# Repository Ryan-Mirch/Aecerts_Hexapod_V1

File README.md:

# Aecerts-Hexapod-V1
# THIS IS A MESSY WIP, USE AT YOUR OWN RISK

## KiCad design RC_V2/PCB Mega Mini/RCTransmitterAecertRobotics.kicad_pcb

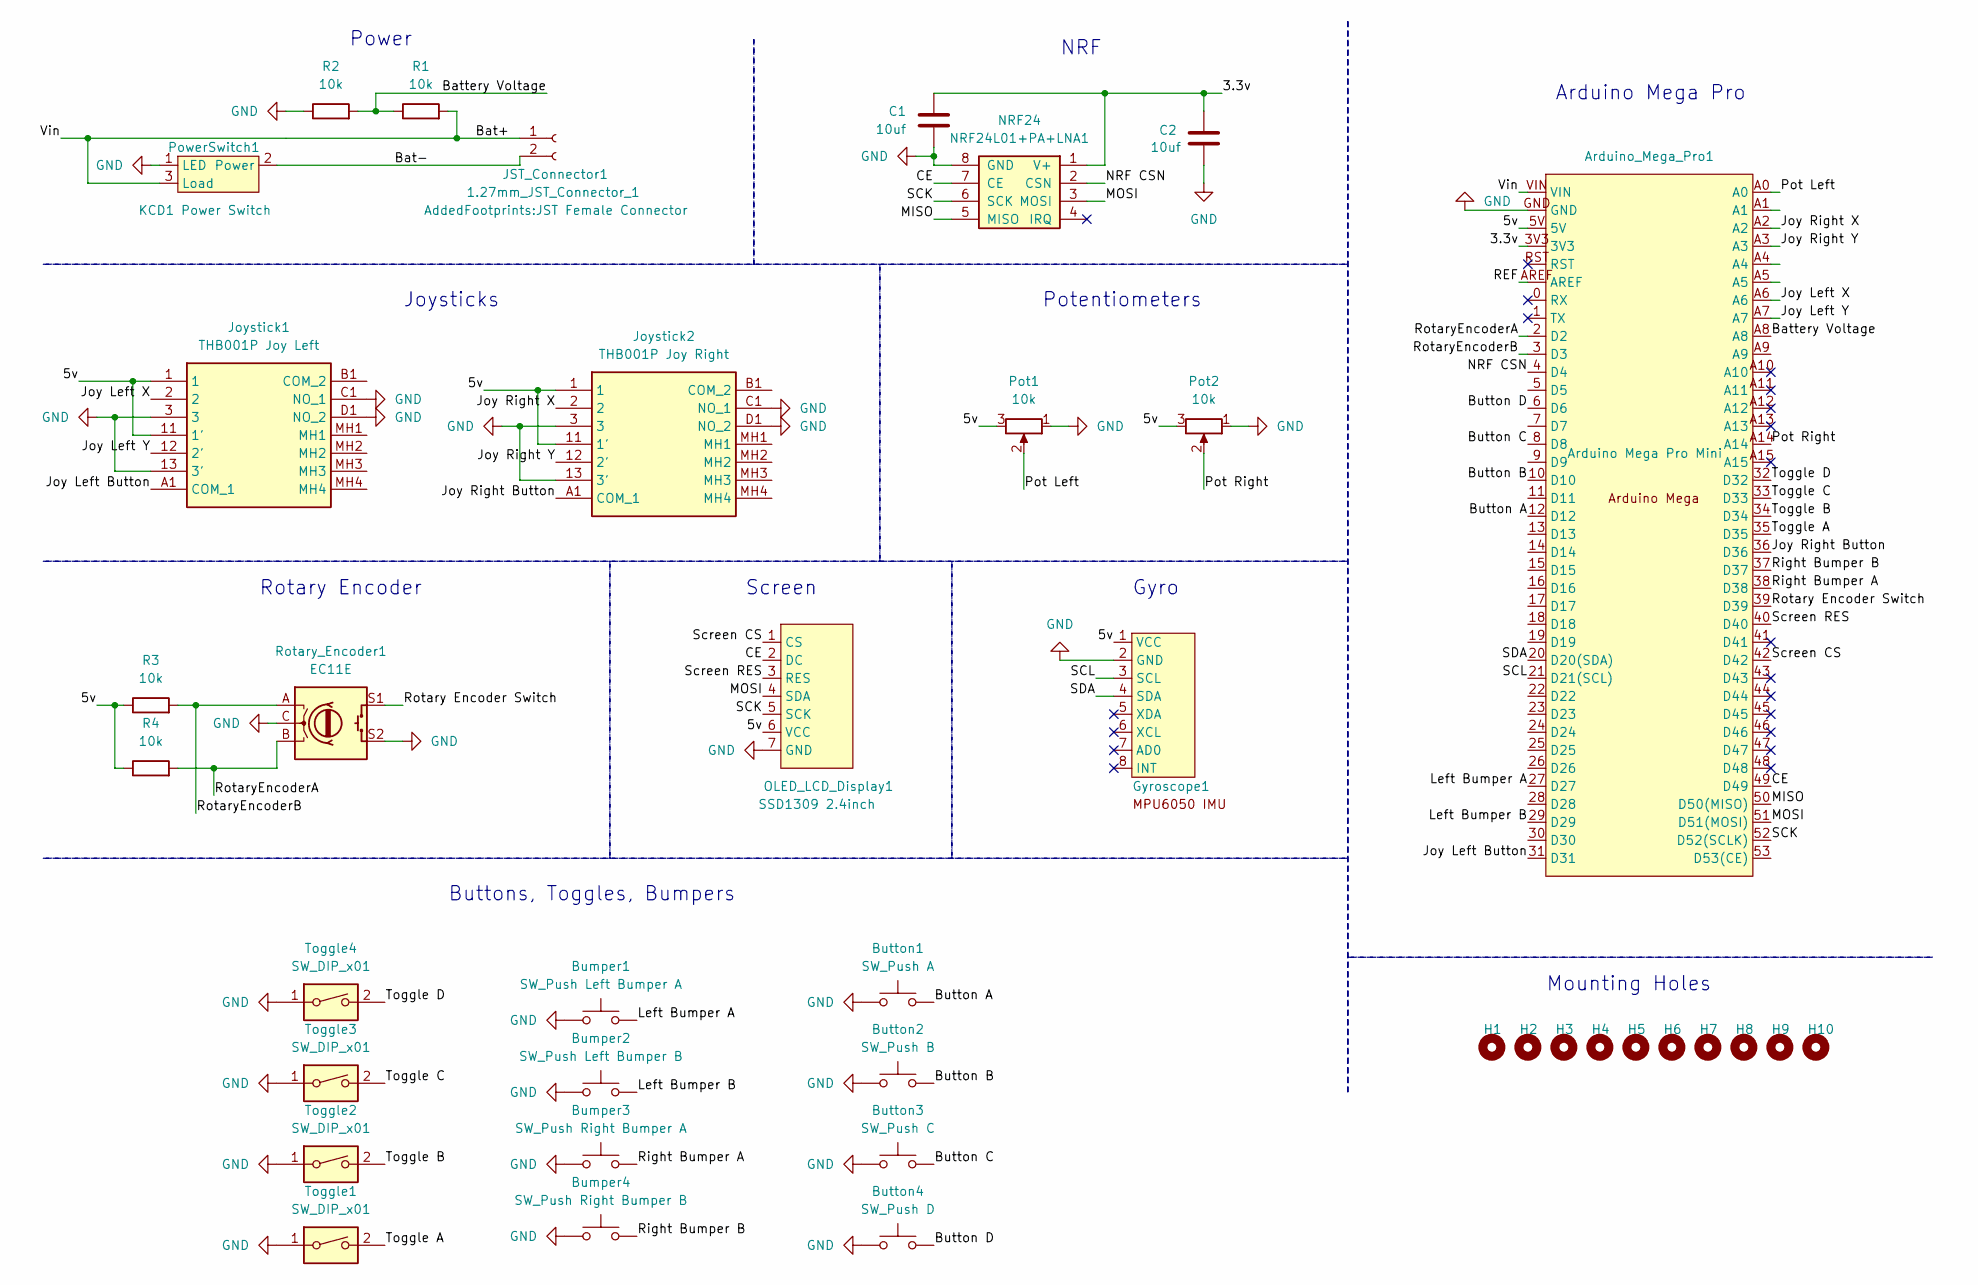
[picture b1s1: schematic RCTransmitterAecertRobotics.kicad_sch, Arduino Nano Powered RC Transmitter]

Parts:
Arduino_Mega_Pro1: Arduino Mega Pro Mini; Arduino Mega Pro
Bumper1: SW_Push Left Bumper A; Bumper Pads
Bumper2: SW_Push Left Bumper B; Bumper Pads
Bumper3: SW_Push Right Bumper A; Bumper Pads
Bumper4: SW_Push Right Bumper B; Bumper Pads
Button1: SW_Push A; SW_PUSH_6mm
Button2: SW_Push B; SW_PUSH_6mm
Button3: SW_Push C; SW_PUSH_6mm
Button4: SW_Push D; SW_PUSH_6mm
C1, C2: 10uf; CP_Radial_D5.0mm_P2.50mm
Gyroscope1: MPU6050 Gyroscope
H1, H2, H3, H4, H5, H6, H7, H8, H9, H10: MountingHole_Pad; MountingHole_3.2mm_M3
JST_Connector1: 1.27mm_JST_Connector_1; JST Female Connector
Joystick1: THB001P Joy Left; THB001P; Mouser Part Number 611-THB001P
Joystick2: THB001P Joy Right; THB001P; Mouser Part Number 611-THB001P
NRF24: NRF24L01+PA+LNA1; NRF24L01+ Antenna
OLED_LCD_Display1: SSD1309 2.4inch; OLED LCD Display SSD1309
Pot1, Pot2: 10k; Potentiometer_Bourns_PTV09A-1_Single_Vertical; Part Number PTV09A-4220F-B103
PowerSwitch1: KCD1 Power Switch; KCD1 Mini Rocker Switch
R1, R2, R3, R4: 10k; R_Axial_DIN0207_L6.3mm_D2.5mm_P7.62mm_Horizontal
Rotary_Encoder1: EC11E; RotaryEncoder_Alps_EC11E-Switch_Vertical_H20mm
Toggle1, Toggle2, Toggle3, Toggle4: SW_DIP_x01; SPST Mini Toggle Switch 2 Pin 2 Position

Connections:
/3.3v: Arduino_Mega_Pro1.3V3, C1.1, C2.1, NRF24.1 (V+)
/5v: Arduino_Mega_Pro1.5V, Gyroscope1.1 (VCC), Joystick1.1, Joystick1.11 (1'), Joystick2.1, Joystick2.11 (1'), OLED_LCD_Display1.6 (VCC), Pot1.3, Pot2.3, R3.1, R4.1
/Bat+: Arduino_Mega_Pro1.VIN, JST_Connector1.1, PowerSwitch1.3 (Load), R1.2
/Bat-: JST_Connector1.2, PowerSwitch1.2 (Power)
/Battery Voltage: Arduino_Mega_Pro1.A8, R1.1, R2.2
/Button A: Arduino_Mega_Pro1.12 (D12), Button1.2
/Button B: Arduino_Mega_Pro1.10 (D10), Button2.2
/Button C: Arduino_Mega_Pro1.8 (D8), Button3.2
/Button D: Arduino_Mega_Pro1.6 (D6), Button4.2
/CE: Arduino_Mega_Pro1.49 (D49), NRF24.7 (CE), OLED_LCD_Display1.2 (DC)
/Joy Left Button: Arduino_Mega_Pro1.31 (D31), Joystick1.A1 (COM_1)
/Joy Left X: Arduino_Mega_Pro1.A6, Joystick1.2
/Joy Left Y: Arduino_Mega_Pro1.A7, Joystick1.12 (2')
/Joy Right Button: Arduino_Mega_Pro1.36 (D36), Joystick2.A1 (COM_1)
/Joy Right X: Arduino_Mega_Pro1.A2, Joystick2.2
/Joy Right Y: Arduino_Mega_Pro1.A3, Joystick2.12 (2')
/Left Bumper A: Arduino_Mega_Pro1.27 (D27), Bumper1.2
/Left Bumper B: Arduino_Mega_Pro1.29 (D29), Bumper2.2
/MISO: Arduino_Mega_Pro1.50 (D50(MISO)), NRF24.5 (MISO)
/MOSI: Arduino_Mega_Pro1.51 (D51(MOSI)), NRF24.3 (MOSI), OLED_LCD_Display1.4 (SDA)
/NRF CSN: Arduino_Mega_Pro1.4 (D4), NRF24.2 (CSN)
/Pot Left: Arduino_Mega_Pro1.A0, Pot1.2
/Pot Right: Arduino_Mega_Pro1.A14, Pot2.2
/REF: Arduino_Mega_Pro1.AREF
/Right Bumper A: Arduino_Mega_Pro1.38 (D38), Bumper3.2
/Right Bumper B: Arduino_Mega_Pro1.37 (D37), Bumper4.2
/Rotary Encoder Switch: Arduino_Mega_Pro1.39 (D39), Rotary_Encoder1.S1
/RotaryEncoderA: Arduino_Mega_Pro1.2 (D2), R4.2, Rotary_Encoder1.B
/RotaryEncoderB: Arduino_Mega_Pro1.3 (D3), R3.2, Rotary_Encoder1.A
/SCK: Arduino_Mega_Pro1.52 (D52(SCLK)), NRF24.6 (SCK), OLED_LCD_Display1.5 (SCK)
/SCL: Arduino_Mega_Pro1.21 (D21(SCL)), Gyroscope1.3 (SCL)
/SDA: Arduino_Mega_Pro1.20 (D20(SDA)), Gyroscope1.4 (SDA)
/Screen CS: Arduino_Mega_Pro1.42 (D42), OLED_LCD_Display1.1 (CS)
/Screen RES: Arduino_Mega_Pro1.40 (D40), OLED_LCD_Display1.3 (RES)
/Toggle A: Arduino_Mega_Pro1.35 (D35), Toggle1.2
/Toggle B: Arduino_Mega_Pro1.34 (D34), Toggle2.2
/Toggle C: Arduino_Mega_Pro1.33 (D33), Toggle3.2
/Toggle D: Arduino_Mega_Pro1.32 (D32), Toggle4.2
GND: Arduino_Mega_Pro1.GND, Bumper1.1, Bumper2.1, Bumper3.1, Bumper4.1, Button1.1, Button2.1, Button3.1, Button4.1, C1.2, C2.2, Gyroscope1.2 (GND), Joystick1.3, Joystick1.13 (3'), Joystick1.C1 (NO_1), Joystick1.D1 (NO_2), Joystick2.3, Joystick2.13 (3'), Joystick2.C1 (NO_1), Joystick2.D1 (NO_2), NRF24.8 (GND), OLED_LCD_Display1.7 (GND), Pot1.1, Pot2.1, PowerSwitch1.1 (LED), R2.1, Rotary_Encoder1.C, Rotary_Encoder1.S2, Toggle1.1, Toggle2.1, Toggle3.1, Toggle4.1

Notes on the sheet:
Screen
NRF
Buttons, Toggles, Bumpers
Gyro
Potentiometers
Mounting Holes
Power
Joysticks
Rotary Encoder
Arduino Mega Pro

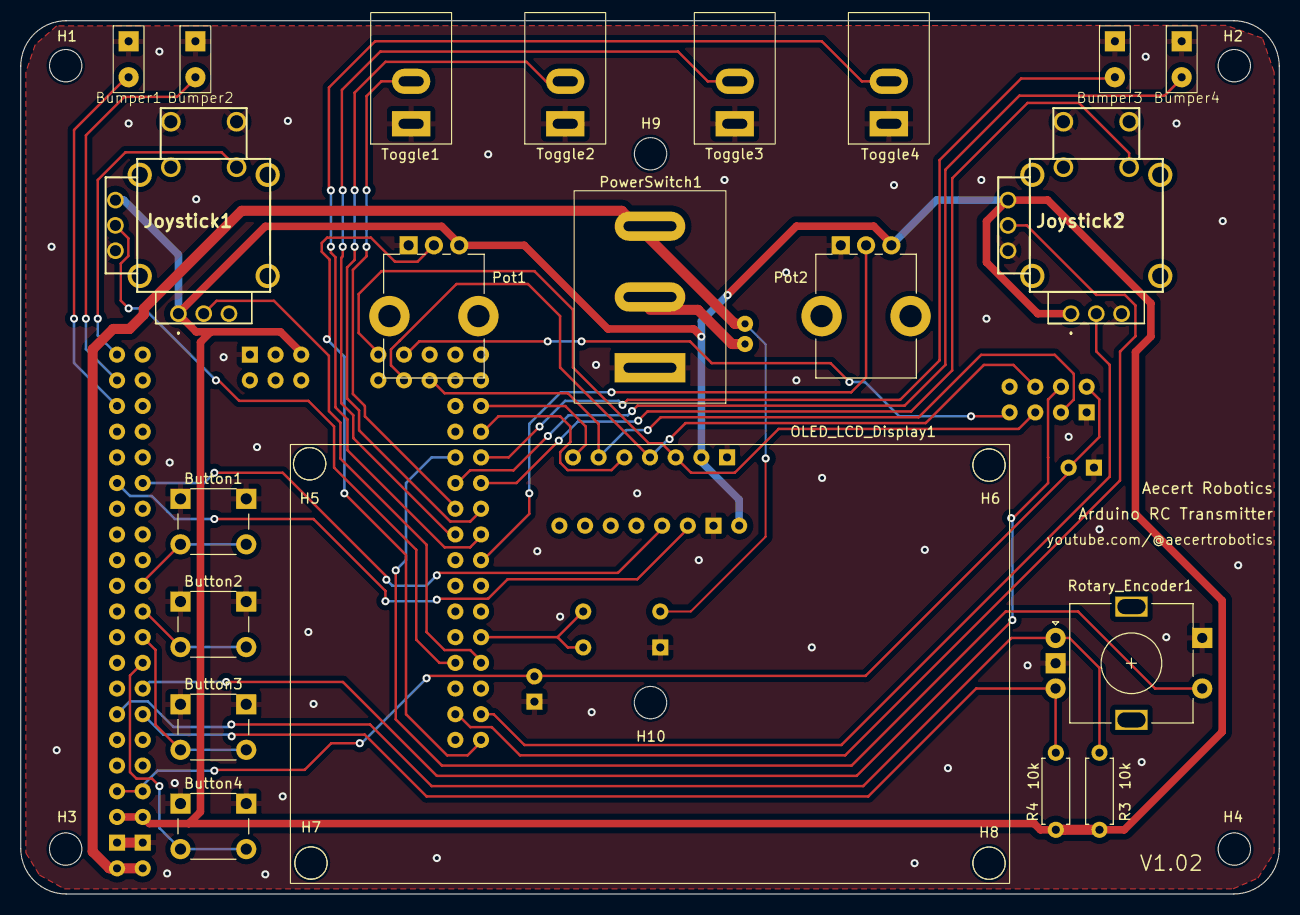
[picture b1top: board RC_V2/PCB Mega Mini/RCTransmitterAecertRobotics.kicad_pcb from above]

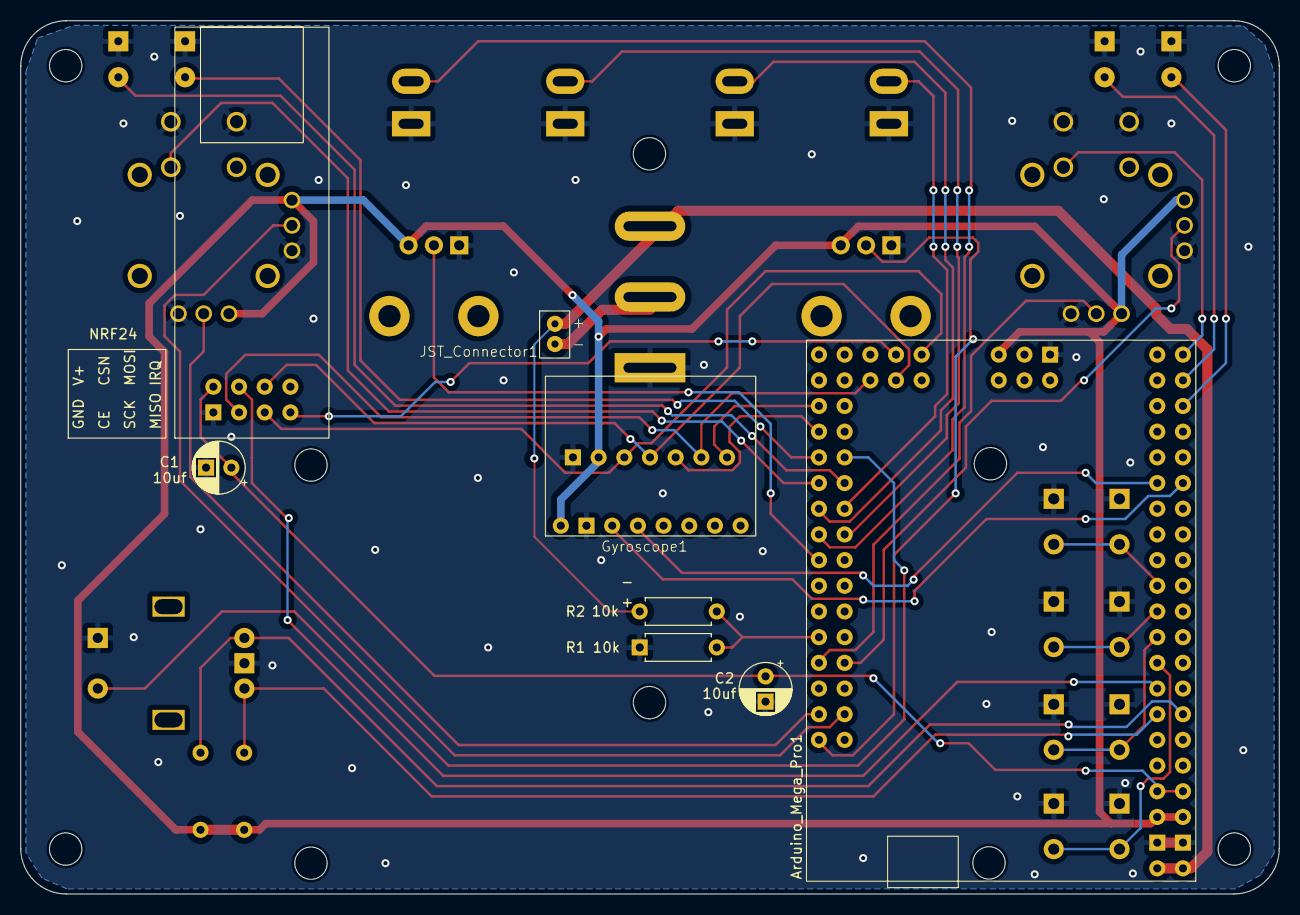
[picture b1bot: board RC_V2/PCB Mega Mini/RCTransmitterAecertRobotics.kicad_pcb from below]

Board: 2 copper layers, 124.5 x 86.4 mm, 39 parts (8 on the bottom side), 38 nets.

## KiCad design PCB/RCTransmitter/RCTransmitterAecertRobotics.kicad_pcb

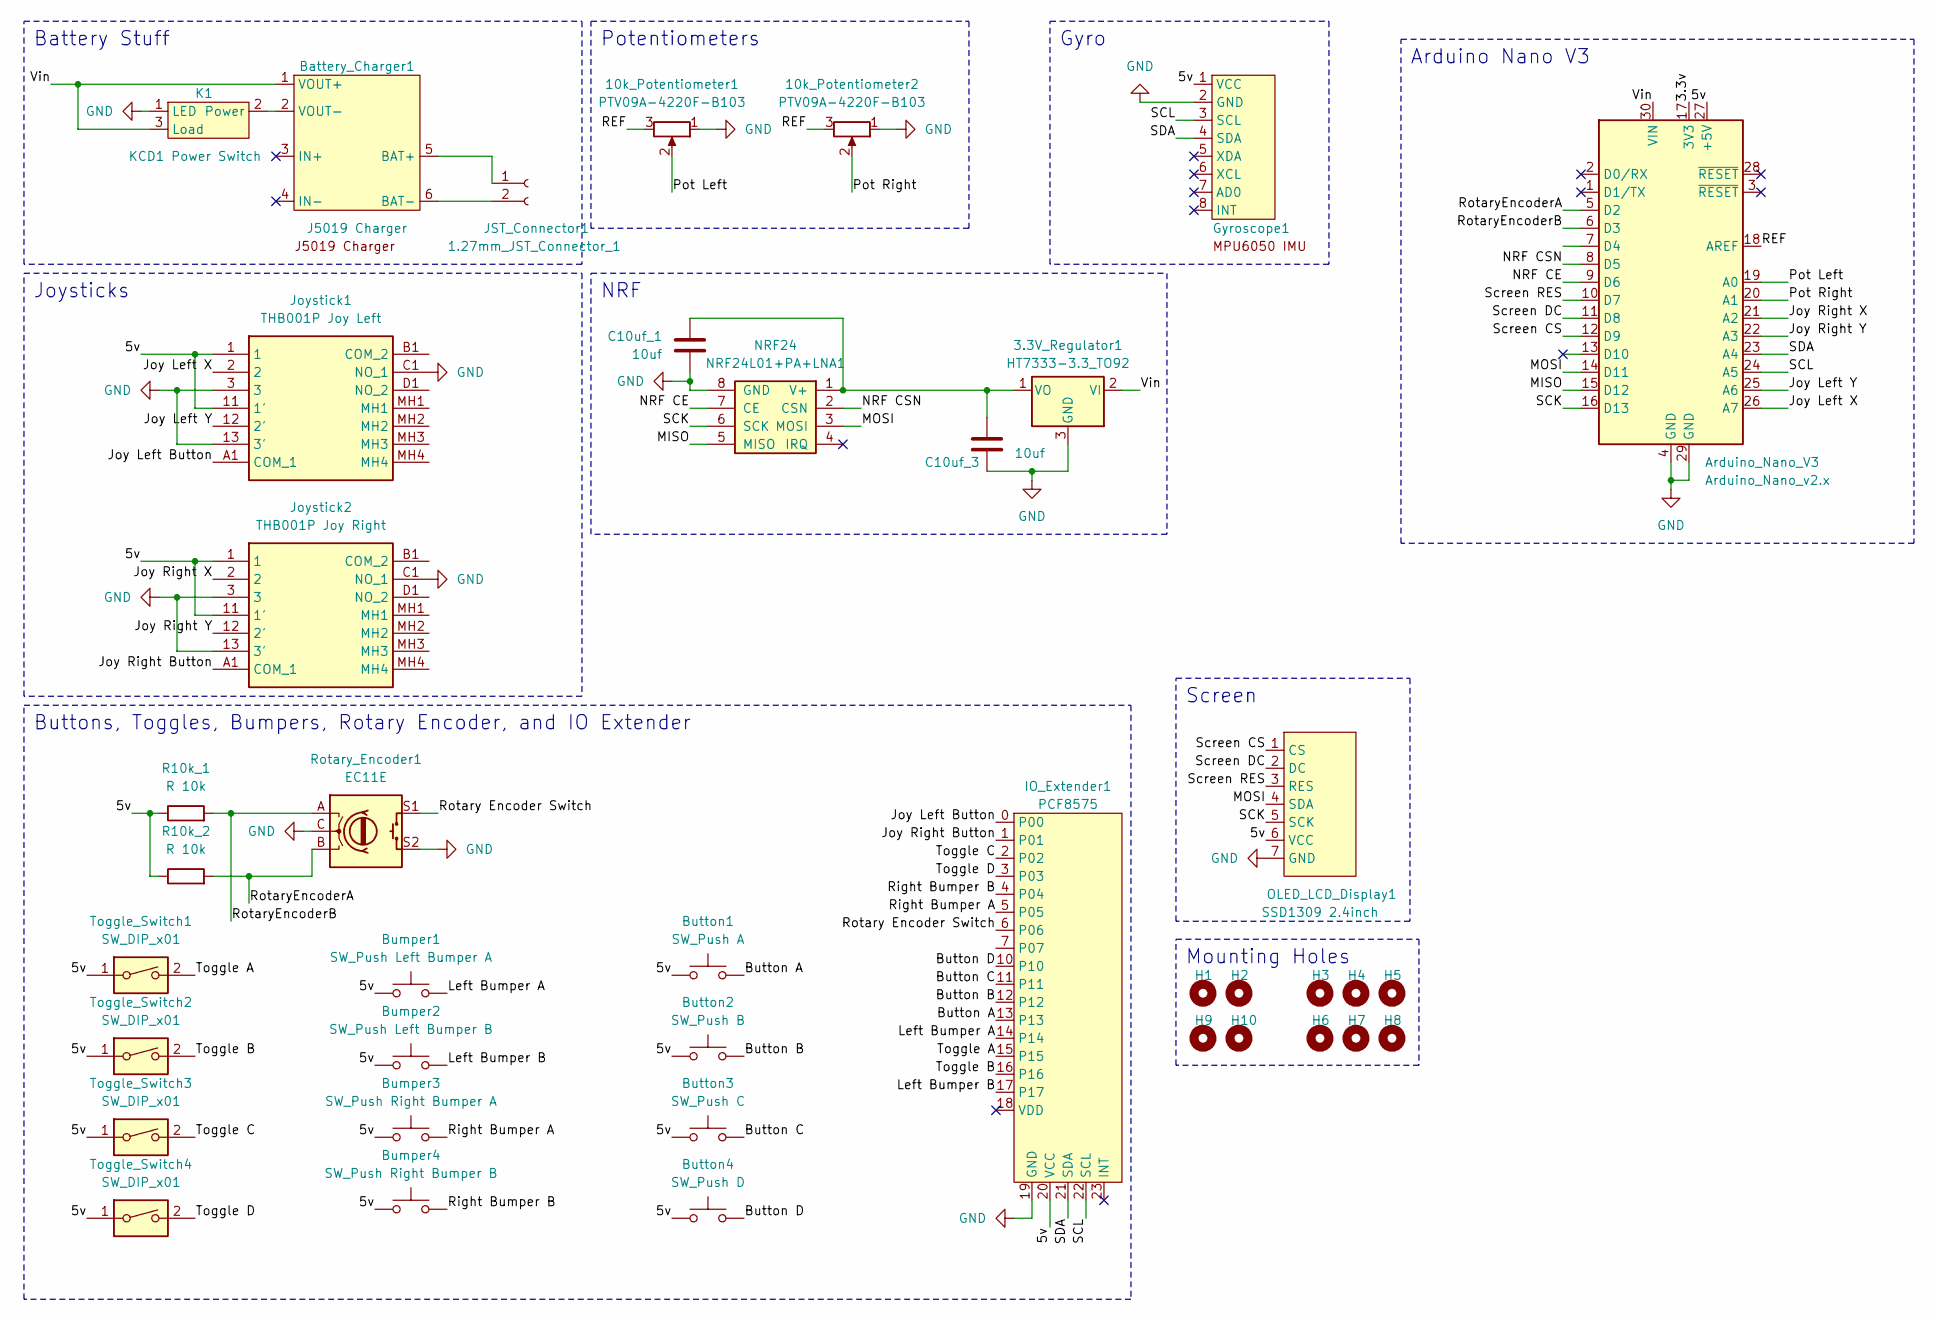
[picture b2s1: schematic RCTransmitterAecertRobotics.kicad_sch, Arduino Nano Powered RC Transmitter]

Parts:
3.3V_Regulator1: HT7333-3.3_TO92; TO-92_Inline
10k_Potentiometer1, 10k_Potentiometer2: PTV09A-4220F-B103; Potentiometer_Bourns_PTV09A-1_Single_Vertical
Arduino_Nano_V3: Arduino_Nano_v2.x; Arduino_Nano
Battery_Charger1: J5019 Charger
Bumper1: SW_Push Left Bumper A; PinHeader_1x02_P2.00mm_Vertical
Bumper2: SW_Push Left Bumper B; PinHeader_1x02_P2.00mm_Vertical
Bumper3: SW_Push Right Bumper A; PinHeader_1x02_P2.00mm_Vertical
Bumper4: SW_Push Right Bumper B; PinHeader_1x02_P2.00mm_Vertical
Button1: SW_Push A; SW_PUSH_6mm
Button2: SW_Push B; SW_PUSH_6mm
Button3: SW_Push C; SW_PUSH_6mm
Button4: SW_Push D; SW_PUSH_6mm
C10uf_1, C10uf_3: 10uf; CP_Radial_D5.0mm_P2.50mm
Gyroscope1: MPU6050 Gyroscope
H1, H2, H3, H4, H5, H6, H7, H8, H9, H10: MountingHole_Pad; MountingHole_3.2mm_M3
IO_Extender1: PCF8575; PCF8575 Module
JST_Connector1: 1.27mm_JST_Connector_1; PinSocket_1x02_P1.27mm_Vertical
Joystick1: THB001P Joy Left; THB001P; Mouser Part Number 611-THB001P
Joystick2: THB001P Joy Right; THB001P; Mouser Part Number 611-THB001P
K1: KCD1 Power Switch; KCD1 Mini Rocker Switch
NRF24: NRF24L01+PA+LNA1; NRF24L01+ Antenna
OLED_LCD_Display1: SSD1309 2.4inch; OLED LCD Display SSD1309
R10k_1, R10k_2: R 10k; R_Axial_DIN0207_L6.3mm_D2.5mm_P7.62mm_Horizontal
Rotary_Encoder1: EC11E; RotaryEncoder_Alps_EC11E-Switch_Vertical_H20mm
Toggle_Switch1, Toggle_Switch2, Toggle_Switch3, Toggle_Switch4: SW_DIP_x01; SPST Mini Toggle Switch 2 Pin 2 Position

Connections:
/3.3v: Arduino_Nano_V3.17 (3V3)
/5v: Arduino_Nano_V3.27 (+5V), Bumper1.1, Bumper2.1, Bumper3.1, Bumper4.1, Button1.1, Button2.1, Button3.1, Button4.1, Gyroscope1.1 (VCC), IO_Extender1.20 (VCC), Joystick1.1, Joystick1.11 (1'), Joystick2.1, Joystick2.11 (1'), OLED_LCD_Display1.6 (VCC), R10k_1.1, R10k_2.1, Toggle_Switch1.1, Toggle_Switch2.1, Toggle_Switch3.1, Toggle_Switch4.1
/Button A: Button1.2, IO_Extender1.13
/Button B: Button2.2, IO_Extender1.12
/Button C: Button3.2, IO_Extender1.11
/Button D: Button4.2, IO_Extender1.10
/Joy Left Button: IO_Extender1.0, Joystick1.A1 (COM_1)
/Joy Left X: Arduino_Nano_V3.26 (A7), Joystick1.2
/Joy Left Y: Arduino_Nano_V3.25 (A6), Joystick1.12 (2')
/Joy Right Button: IO_Extender1.1, Joystick2.A1 (COM_1)
/Joy Right X: Arduino_Nano_V3.21 (A2), Joystick2.2
/Joy Right Y: Arduino_Nano_V3.22 (A3), Joystick2.12 (2')
/Left Bumper A: Bumper1.2, IO_Extender1.14
/Left Bumper B: Bumper2.2, IO_Extender1.17
/MISO: Arduino_Nano_V3.15 (D12), NRF24.5 (MISO)
/MOSI: Arduino_Nano_V3.14 (D11), NRF24.3 (MOSI), OLED_LCD_Display1.4 (SDA)
/NRF CE: Arduino_Nano_V3.9 (D6), NRF24.7 (CE)
/NRF CSN: Arduino_Nano_V3.8 (D5), NRF24.2 (CSN)
/Pot Left: 10k_Potentiometer1.2, Arduino_Nano_V3.19 (A0)
/Pot Right: 10k_Potentiometer2.2, Arduino_Nano_V3.20 (A1)
/REF: 10k_Potentiometer1.3, 10k_Potentiometer2.3, Arduino_Nano_V3.18 (AREF)
/Right Bumper A: Bumper3.2, IO_Extender1.5
/Right Bumper B: Bumper4.2, IO_Extender1.4
/Rotary Encoder Switch: IO_Extender1.6, Rotary_Encoder1.S1
/RotaryEncoderA: Arduino_Nano_V3.5 (D2), R10k_2.2, Rotary_Encoder1.B
/RotaryEncoderB: Arduino_Nano_V3.6 (D3), R10k_1.2, Rotary_Encoder1.A
/SCK: Arduino_Nano_V3.16 (D13), NRF24.6 (SCK), OLED_LCD_Display1.5 (SCK)
/SCL: Arduino_Nano_V3.24 (A5), Gyroscope1.3 (SCL), IO_Extender1.22 (SCL)
/SDA: Arduino_Nano_V3.23 (A4), Gyroscope1.4 (SDA), IO_Extender1.21 (SDA)
/Screen CS: Arduino_Nano_V3.12 (D9), OLED_LCD_Display1.1 (CS)
/Screen DC: Arduino_Nano_V3.11 (D8), OLED_LCD_Display1.2 (DC)
/Screen RES: Arduino_Nano_V3.10 (D7), OLED_LCD_Display1.3 (RES)
/Toggle A: IO_Extender1.15, Toggle_Switch1.2
/Toggle B: IO_Extender1.16, Toggle_Switch2.2
/Toggle C: IO_Extender1.2, Toggle_Switch3.2
/Toggle D: IO_Extender1.3, Toggle_Switch4.2
/Vin: 3.3V_Regulator1.2 (VI), Arduino_Nano_V3.30 (VIN), Battery_Charger1.1 (VOUT+), K1.3 (Load)
GND: 3.3V_Regulator1.3 (GND), 10k_Potentiometer1.1, 10k_Potentiometer2.1, Arduino_Nano_V3.4 (GND), Arduino_Nano_V3.29 (GND), C10uf_1.2, C10uf_3.2, Gyroscope1.2 (GND), IO_Extender1.19 (GND), Joystick1.3, Joystick1.13 (3'), Joystick1.C1 (NO_1), Joystick2.3, Joystick2.13 (3'), Joystick2.C1 (NO_1), K1.1 (LED), NRF24.8 (GND), OLED_LCD_Display1.7 (GND), Rotary_Encoder1.C, Rotary_Encoder1.S2
unnamed: 3.3V_Regulator1.1 (VO), C10uf_1.1, C10uf_3.1, NRF24.1 (V+)
unnamed: Battery_Charger1.5 (BAT+), JST_Connector1.1
unnamed: Battery_Charger1.6 (BAT-), JST_Connector1.2
unnamed: Battery_Charger1.2 (VOUT-), K1.2 (Power)

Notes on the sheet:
Screen
NRF
Buttons, Toggles, Bumpers, Rotary Encoder, and IO Extender
Gyro
Potentiometers
Mounting Holes
Battery Stuff
Joysticks
Arduino Nano V3

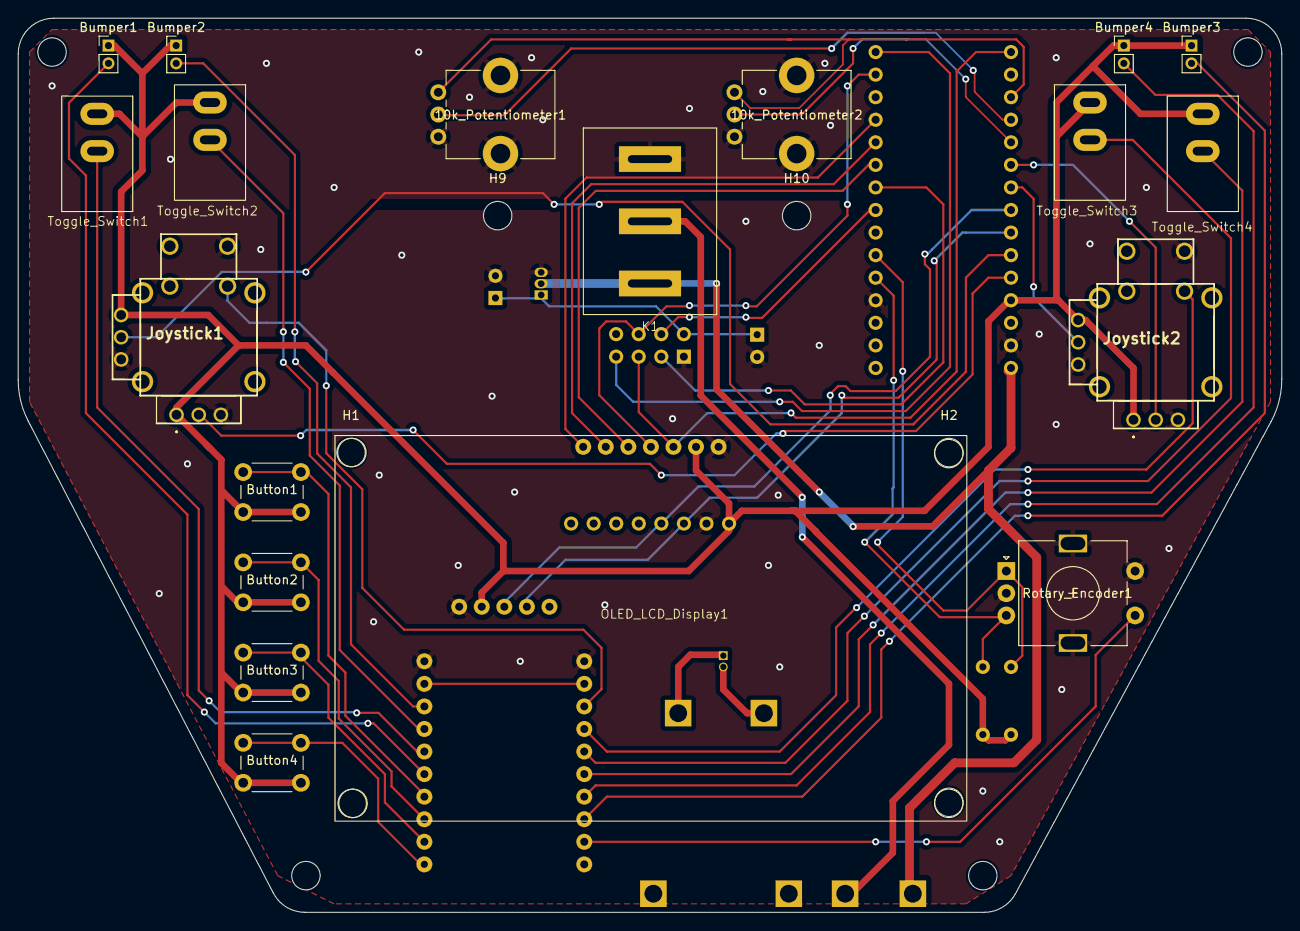
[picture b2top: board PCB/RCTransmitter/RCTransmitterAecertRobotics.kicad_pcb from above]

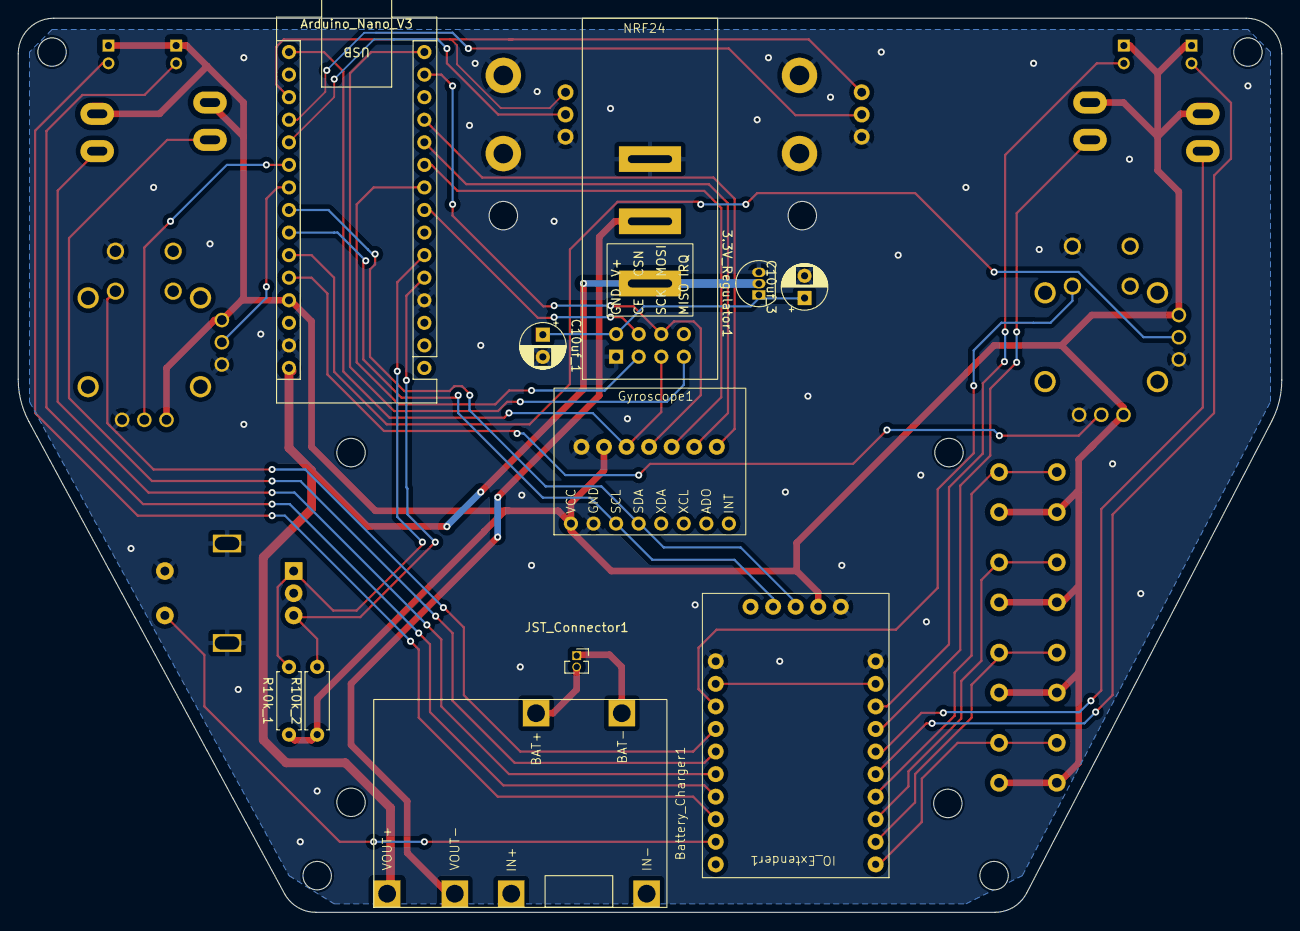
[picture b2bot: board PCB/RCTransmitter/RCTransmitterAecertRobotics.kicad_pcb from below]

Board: 2 copper layers, 142.2 x 100.6 mm, 40 parts (11 on the bottom side), 41 nets.

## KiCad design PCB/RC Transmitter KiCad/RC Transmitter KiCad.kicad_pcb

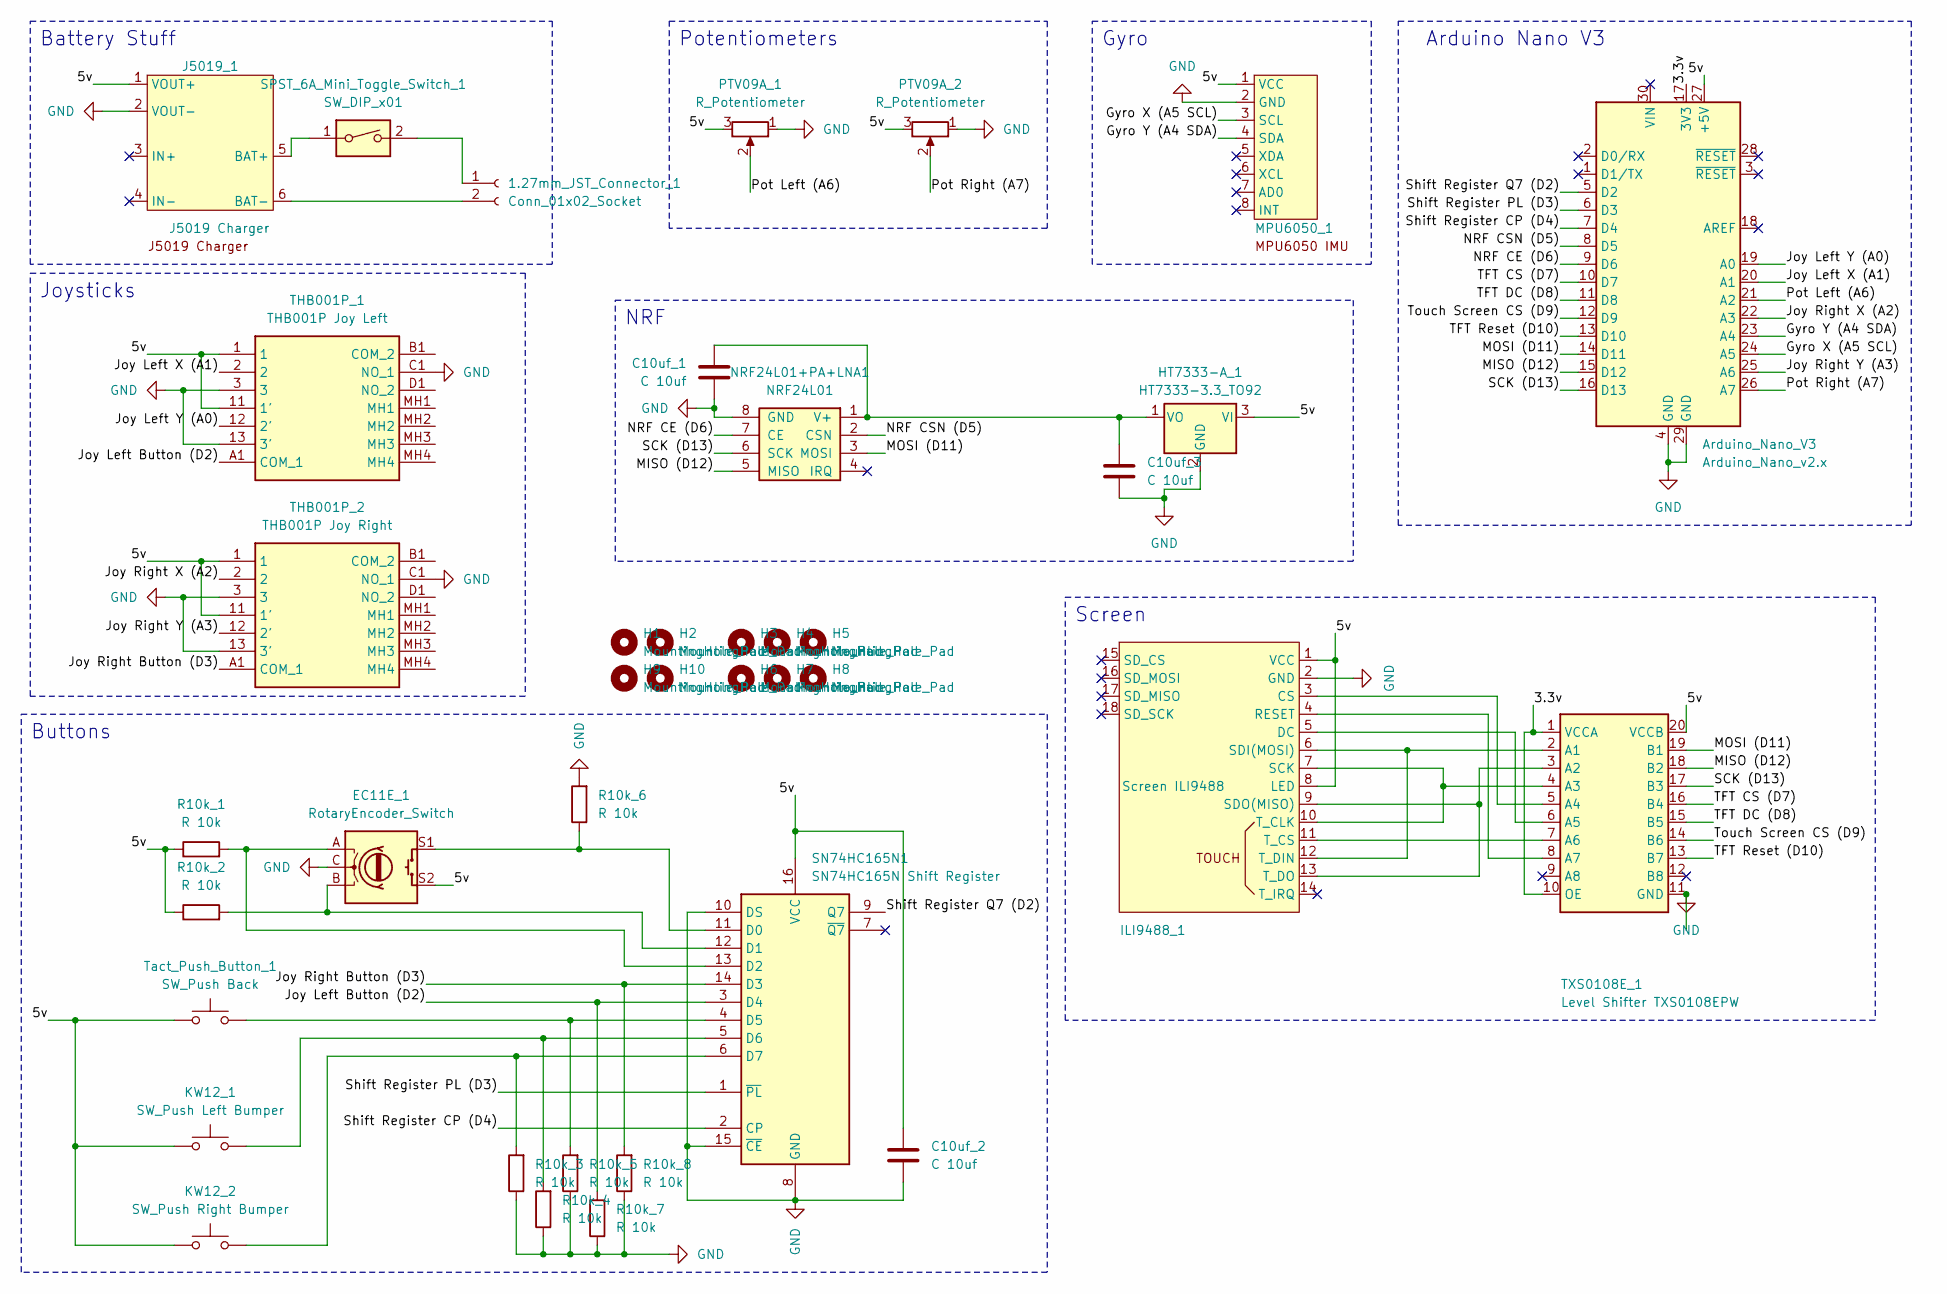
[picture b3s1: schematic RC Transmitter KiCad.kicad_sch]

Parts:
1.27mm_JST_Connector_1: Conn_01x02_Socket; PinSocket_1x02_P1.27mm_Vertical
Arduino_Nano_V3: Arduino_Nano_v2.x; Arduino_Nano
C10uf_1, C10uf_2, C10uf_3: C 10uf; CP_Radial_D5.0mm_P2.50mm
EC11E_1: RotaryEncoder_Switch; RotaryEncoder_Alps_EC11E-Switch_Vertical_H20mm
H1, H2, H9, H10: MountingHole_Pad; MountingHole_2.2mm_M2
H3, H4, H5, H6, H7, H8: MountingHole_Pad; MountingHole_3.2mm_M3
HT7333-A_1: HT7333-3.3_TO92; TO-92_Inline
ILI9488_1: Screen ILI9488; 3.5 Inch Screen SPI_Module_ILI9488
J5019_1: J5019 Charger
KW12_1: SW_Push Left Bumper; PinHeader_1x02_P2.00mm_Vertical
KW12_2: SW_Push Right Bumper; PinHeader_1x02_P2.00mm_Vertical
MPU6050_1: MPU6050 Gyroscope
NRF24L01+PA+LNA1: NRF24L01; NRF24L01+ Antenna
R10k_1, R10k_2, R10k_3, R10k_4, R10k_5, R10k_6, R10k_7, R10k_8: R 10k; R_Axial_DIN0207_L6.3mm_D2.5mm_P7.62mm_Horizontal
SN74HC165N1: SN74HC165N Shift Register; DIP794W45P254L1969H508Q16
SPST_6A_Mini_Toggle_Switch_1: SW_DIP_x01; PinHeader_1x02_P2.00mm_Vertical
THB001P_1: THB001P Joy Left; THB001P; Mouser Part Number 611-THB001P
THB001P_2: THB001P Joy Right; THB001P; Mouser Part Number 611-THB001P
TXS0108E_1: Level Shifter TXS0108EPW; HW-221 Level Shifter
Tact_Push_Button_1: SW_Push Back; SW_PUSH_6mm
‎PTV09A_1, ‎PTV09A_2: R_Potentiometer; Potentiometer_Bourns_PTV09A-1_Single_Vertical

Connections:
/3.3v: Arduino_Nano_V3.17 (3V3), TXS0108E_1.1 (VCCA), TXS0108E_1.10 (OE)
/5v: Arduino_Nano_V3.27 (+5V), C10uf_2.1, EC11E_1.S2, HT7333-A_1.3 (VI), ILI9488_1.1 (VCC), ILI9488_1.8 (LED), J5019_1.1 (VOUT+), KW12_1.1, KW12_2.1, MPU6050_1.1 (VCC), R10k_1.1, R10k_2.1, SN74HC165N1.16 (VCC), THB001P_1.1, THB001P_1.11 (1'), THB001P_2.1, THB001P_2.11 (1'), TXS0108E_1.20 (VCCB), Tact_Push_Button_1.1, ‎PTV09A_1.3, ‎PTV09A_2.3
/Gyro X (A5 SCL): Arduino_Nano_V3.24 (A5), MPU6050_1.3 (SCL)
/Gyro Y (A4 SDA): Arduino_Nano_V3.23 (A4), MPU6050_1.4 (SDA)
/Joy Left Button (D2): R10k_7.2, SN74HC165N1.3 (D4), THB001P_1.A1 (COM_1)
/Joy Left X (A1): Arduino_Nano_V3.20 (A1), THB001P_1.2
/Joy Left Y (A0): Arduino_Nano_V3.19 (A0), THB001P_1.12 (2')
/Joy Right Button (D3): R10k_8.2, SN74HC165N1.14 (D3), THB001P_2.A1 (COM_1)
/Joy Right X (A2): Arduino_Nano_V3.22 (A3), THB001P_2.2
/Joy Right Y (A3): Arduino_Nano_V3.25 (A6), THB001P_2.12 (2')
/MISO (D12): Arduino_Nano_V3.15 (D12), NRF24L01+PA+LNA1.5 (MISO), TXS0108E_1.18 (B2)
/MOSI (D11): Arduino_Nano_V3.14 (D11), NRF24L01+PA+LNA1.3 (MOSI), TXS0108E_1.19 (B1)
/NRF CE (D6): Arduino_Nano_V3.9 (D6), NRF24L01+PA+LNA1.7 (CE)
/NRF CSN (D5): Arduino_Nano_V3.8 (D5), NRF24L01+PA+LNA1.2 (CSN)
/Pot Left (A6): Arduino_Nano_V3.21 (A2), ‎PTV09A_1.2
/Pot Right (A7): Arduino_Nano_V3.26 (A7), ‎PTV09A_2.2
/SCK (D13): Arduino_Nano_V3.16 (D13), NRF24L01+PA+LNA1.6 (SCK), TXS0108E_1.17 (B3)
/Shift Register CP (D4): Arduino_Nano_V3.7 (D4), SN74HC165N1.2 (CP)
/Shift Register PL (D3): Arduino_Nano_V3.6 (D3), SN74HC165N1.1 (~PL)
/Shift Register Q7 (D2): Arduino_Nano_V3.5 (D2), SN74HC165N1.9 (Q7)
/TFT CS (D7): Arduino_Nano_V3.10 (D7), TXS0108E_1.16 (B4)
/TFT DC (D8): Arduino_Nano_V3.11 (D8), TXS0108E_1.15 (B5)
/TFT Reset (D10): Arduino_Nano_V3.13 (D10), TXS0108E_1.13 (B7)
/Touch Screen CS (D9): Arduino_Nano_V3.12 (D9), TXS0108E_1.14 (B6)
GND: Arduino_Nano_V3.4 (GND), Arduino_Nano_V3.29 (GND), C10uf_1.2, C10uf_2.2, C10uf_3.2, EC11E_1.C, HT7333-A_1.2 (GND), ILI9488_1.2 (GND), J5019_1.2 (VOUT-), MPU6050_1.2 (GND), NRF24L01+PA+LNA1.8 (GND), R10k_3.1, R10k_4.1, R10k_5.1, R10k_6.2, R10k_7.1, R10k_8.1, SN74HC165N1.8 (GND), SN74HC165N1.10 (DS), SN74HC165N1.15 (~CE), THB001P_1.3, THB001P_1.13 (3'), THB001P_1.C1 (NO_1), THB001P_2.3, THB001P_2.13 (3'), THB001P_2.C1 (NO_1), TXS0108E_1.11 (GND), ‎PTV09A_1.1, ‎PTV09A_2.1
unnamed: 1.27mm_JST_Connector_1.1, SPST_6A_Mini_Toggle_Switch_1.2
unnamed: 1.27mm_JST_Connector_1.2, J5019_1.6 (BAT-)
unnamed: C10uf_1.1, C10uf_3.1, HT7333-A_1.1 (VO), NRF24L01+PA+LNA1.1 (V+)
unnamed: ILI9488_1.3 (CS), TXS0108E_1.5 (A4)
unnamed: ILI9488_1.5 (DC), TXS0108E_1.6 (A5)
unnamed: ILI9488_1.4 (RESET), TXS0108E_1.8 (A7)
unnamed: ILI9488_1.7 (SCK), ILI9488_1.10 (T_CLK), TXS0108E_1.4 (A3)
unnamed: ILI9488_1.6 (SDI(MOSI)), ILI9488_1.12 (T_DIN), TXS0108E_1.2 (A1)
unnamed: ILI9488_1.9 (SDO(MISO)), ILI9488_1.13 (T_DO), TXS0108E_1.3 (A2)
unnamed: ILI9488_1.11 (T_CS), TXS0108E_1.7 (A6)
unnamed: J5019_1.5 (BAT+), SPST_6A_Mini_Toggle_Switch_1.1
unnamed: EC11E_1.S1, R10k_6.1, SN74HC165N1.11 (D0)
unnamed: EC11E_1.B, R10k_2.2, SN74HC165N1.12 (D1)
unnamed: EC11E_1.A, R10k_1.2, SN74HC165N1.13 (D2)
unnamed: R10k_5.2, SN74HC165N1.4 (D5), Tact_Push_Button_1.2
unnamed: KW12_1.2, R10k_4.2, SN74HC165N1.5 (D6)
unnamed: KW12_2.2, R10k_3.2, SN74HC165N1.6 (D7)

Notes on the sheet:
Screen
NRF
Buttons
Gyro
Potentiometers
Battery Stuff
Joysticks
Arduino Nano V3

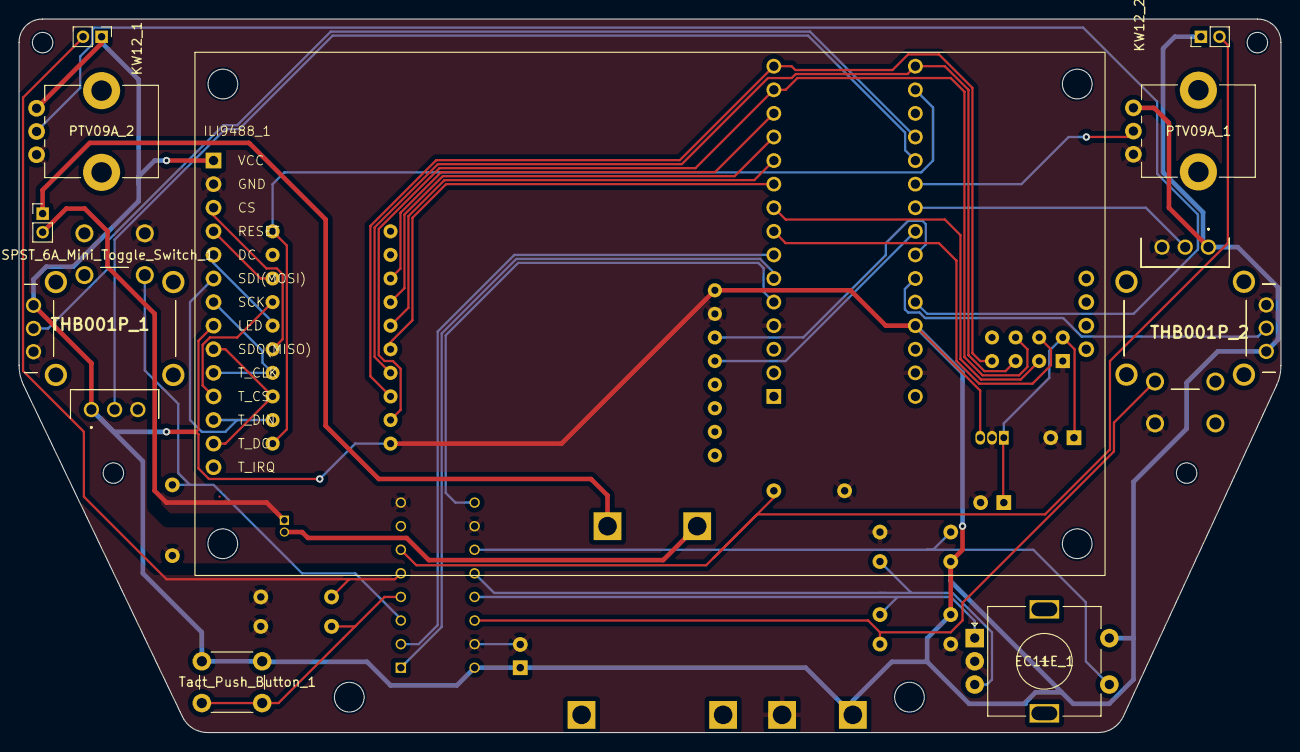
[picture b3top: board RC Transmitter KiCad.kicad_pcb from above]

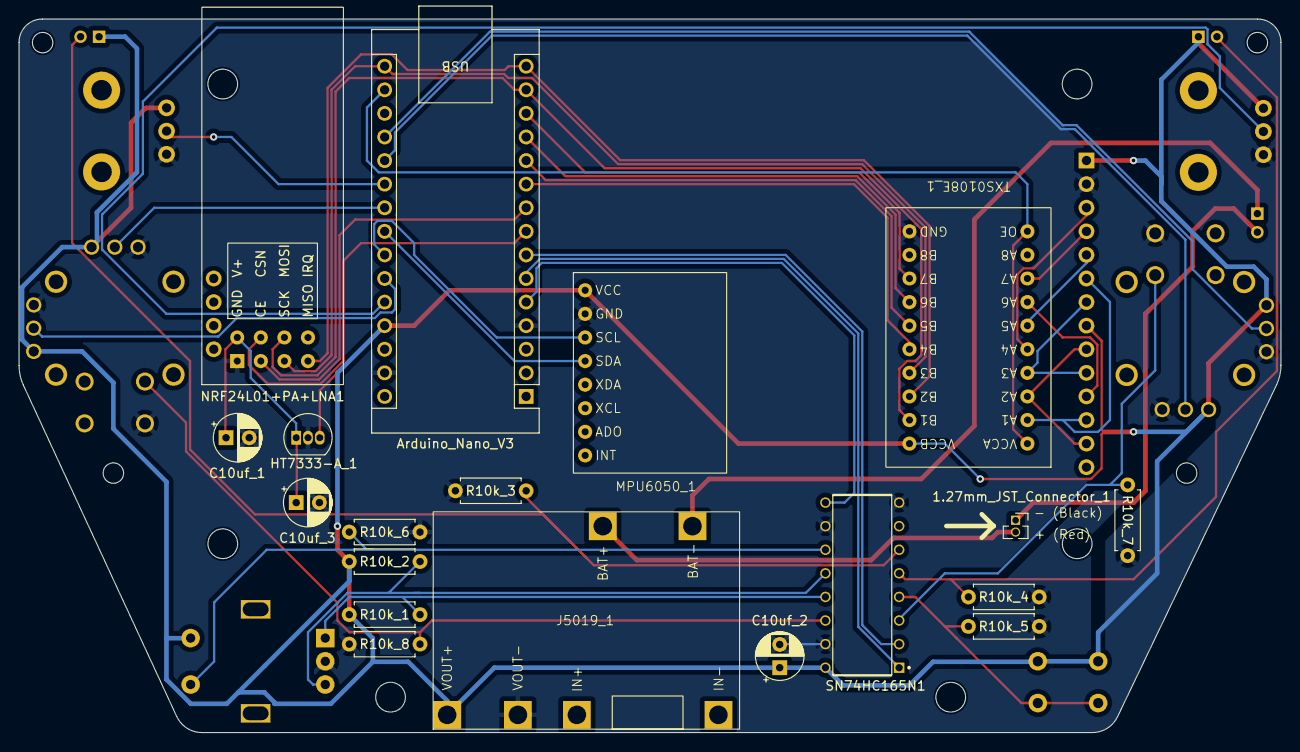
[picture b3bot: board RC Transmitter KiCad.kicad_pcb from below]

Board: 2 copper layers, 135.9 x 76.8 mm, 39 parts (19 on the bottom side), 42 nets.
